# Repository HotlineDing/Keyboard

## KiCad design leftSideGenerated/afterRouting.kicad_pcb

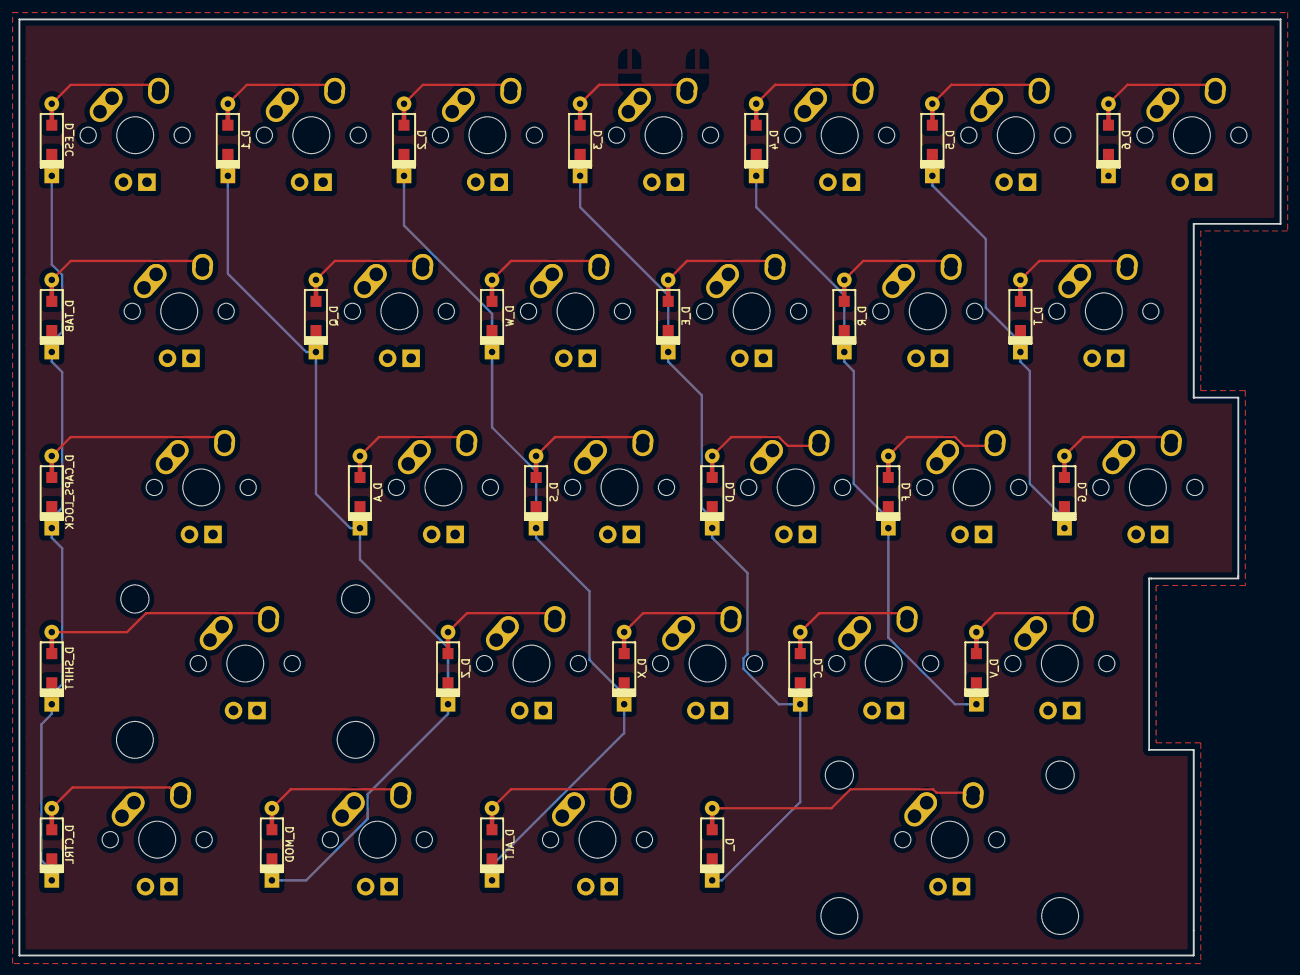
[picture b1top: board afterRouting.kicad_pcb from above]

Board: 2 copper layers, 136.4 x 101.2 mm, 56 parts (0 on the bottom side), 34 nets.

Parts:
D_, D_1, D_2, D_3, D_4, D_5, D_6: D; D_SOD123_axial
D_A: D; D_SOD123_axial
D_ALT: D; D_SOD123_axial
D_C: D; D_SOD123_axial
D_CAPS_LOCK: D; D_SOD123_axial
D_CTRL: D; D_SOD123_axial
D_D: D; D_SOD123_axial
D_E: D; D_SOD123_axial
D_ESC: D; D_SOD123_axial
D_F: D; D_SOD123_axial
D_G: D; D_SOD123_axial
D_MOD: D; D_SOD123_axial
D_Q: D; D_SOD123_axial
D_R: D; D_SOD123_axial
D_S: D; D_SOD123_axial
D_SHIFT: D; D_SOD123_axial
D_T: D; D_SOD123_axial
D_TAB: D; D_SOD123_axial
D_V: D; D_SOD123_axial
D_W: D; D_SOD123_axial
D_X: D; D_SOD123_axial
D_Z: D; D_SOD123_axial
K_: KEYSW; MX-2.75U-NoLED
K_1, K_2, K_3, K_4, K_5, K_6: KEYSW; MX-1U-NoLED
K_A: KEYSW; MX-1U-NoLED
K_ALT: KEYSW; MX-1.25U-NoLED
K_C: KEYSW; MX-1U-NoLED
K_CAPS_LOCK: KEYSW; MX-1.75U-NoLED
K_CTRL: KEYSW; MX-1.25U-NoLED
K_D: KEYSW; MX-1U-NoLED
K_E: KEYSW; MX-1U-NoLED
K_ESC: KEYSW; MX-1U-NoLED
K_F: KEYSW; MX-1U-NoLED
K_G: KEYSW; MX-1U-NoLED
K_MOD: KEYSW; MX-1.25U-NoLED
K_Q: KEYSW; MX-1U-NoLED
K_R: KEYSW; MX-1U-NoLED
K_S: KEYSW; MX-1U-NoLED
K_SHIFT: KEYSW; MX-2.25U-NoLED
K_T: KEYSW; MX-1U-NoLED
K_TAB: KEYSW; MX-1.5U-NoLED
K_V: KEYSW; MX-1U-NoLED
K_W: KEYSW; MX-1U-NoLED
K_X: KEYSW; MX-1U-NoLED
K_Z: KEYSW; MX-1U-NoLED

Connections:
/col0: D_CAPS_LOCK.1, D_CTRL.1, D_ESC.1, D_SHIFT.1, D_TAB.1
/col1: D_1.1, D_A.1, D_MOD.1, D_Q.1, D_Z.1
/col2: D_2.1, D_ALT.1, D_S.1, D_W.1, D_X.1
/col3: D_.1, D_3.1, D_C.1, D_D.1, D_E.1
/col4: D_4.1, D_F.1, D_R.1, D_V.1
/col5: D_5.1, D_G.1, D_T.1
unnamed: D_1.2, K_1.2
unnamed: D_2.2, K_2.2
unnamed: D_3.2, K_3.2
unnamed: D_4.2, K_4.2
unnamed: D_5.2, K_5.2
unnamed: D_6.2, K_6.2
unnamed: D_.2, K_.2
unnamed: D_A.2, K_A.2
unnamed: D_ALT.2, K_ALT.2
unnamed: D_C.2, K_C.2
unnamed: D_CAPS_LOCK.2, K_CAPS_LOCK.2
unnamed: D_CTRL.2, K_CTRL.2
unnamed: D_D.2, K_D.2
unnamed: D_E.2, K_E.2
unnamed: D_ESC.2, K_ESC.2
unnamed: D_F.2, K_F.2
unnamed: D_G.2, K_G.2
unnamed: D_MOD.2, K_MOD.2
unnamed: D_Q.2, K_Q.2
unnamed: D_R.2, K_R.2
unnamed: D_S.2, K_S.2
unnamed: D_SHIFT.2, K_SHIFT.2
unnamed: D_T.2, K_T.2
unnamed: D_TAB.2, K_TAB.2
unnamed: D_V.2, K_V.2
unnamed: D_W.2, K_W.2
unnamed: D_X.2, K_X.2
unnamed: D_Z.2, K_Z.2
